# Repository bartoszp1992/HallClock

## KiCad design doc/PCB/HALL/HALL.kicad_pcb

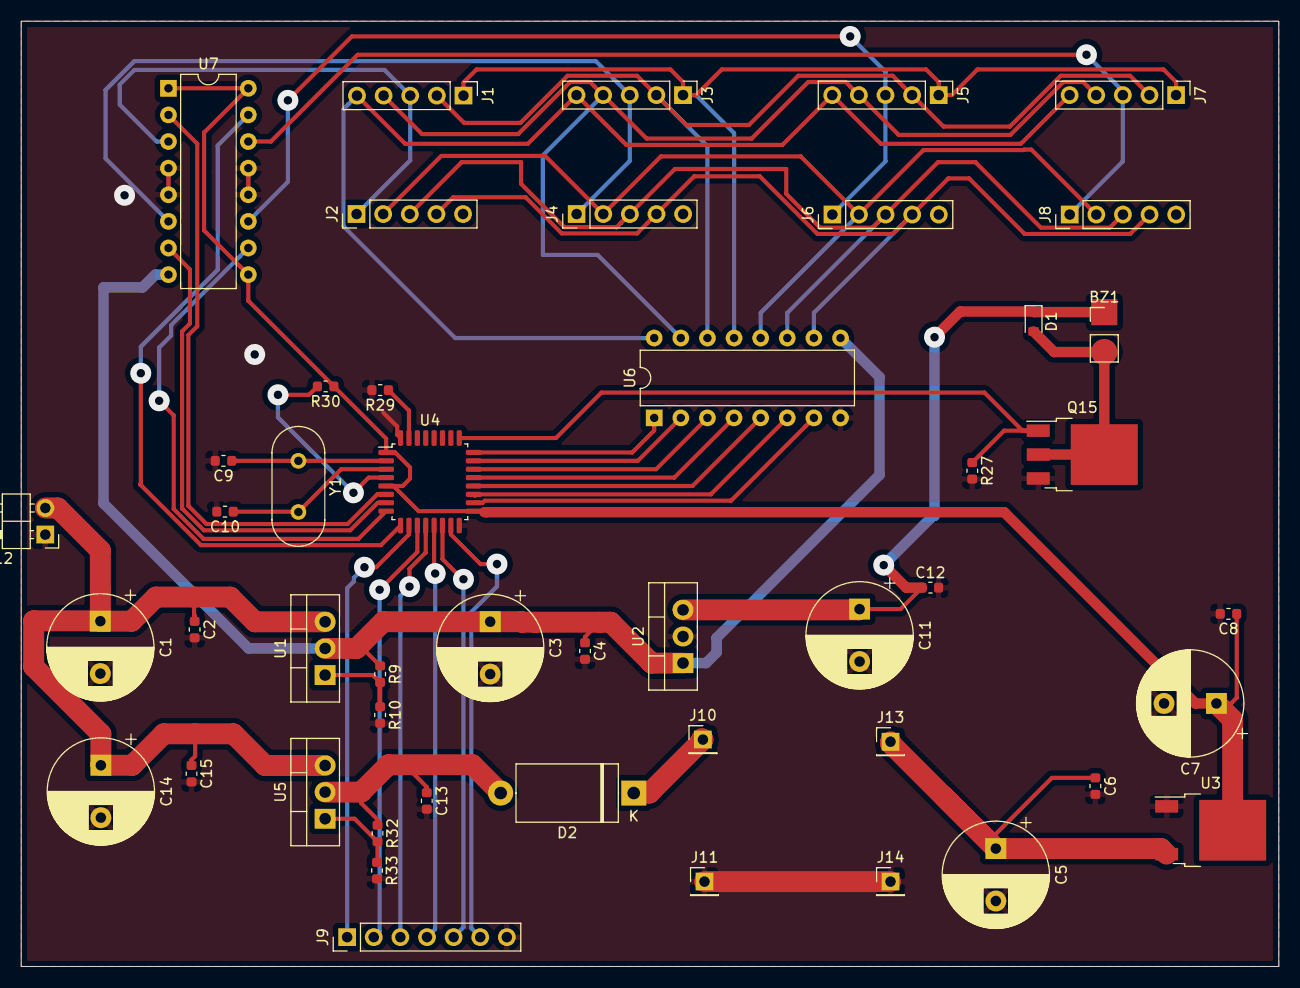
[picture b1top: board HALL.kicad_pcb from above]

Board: 2 copper layers, 120.0 x 90.2 mm, 48 parts (0 on the bottom side), 44 nets.

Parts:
BZ1: BELL; PinHeader_1x02_P2.54mm_Vertical
C1, C3, C5, C7, C11, C14: 10u; CP_Radial_D10.0mm_P5.00mm
C2, C4, C6, C8, C12, C13, C15: 100n; C_0603_1608Metric
C9, C10: 22p; C_0603_1608Metric
D1: 1n4148; D_SOD-110
D2: SR540; D_DO-27_P12.70mm_Horizontal
J1, J3, J5, J7: Conn_01x05_Female; PinHeader_1x05_P2.54mm_Vertical
J2: Digit1; PinHeader_1x05_P2.54mm_Vertical
J4: Digit2; PinHeader_1x05_P2.54mm_Vertical
J6: Digit3; PinHeader_1x05_P2.54mm_Vertical
J8: Digit4; PinHeader_1x05_P2.54mm_Vertical
J9: PILOT; PinHeader_1x07_P2.54mm_Vertical
J10: CHIN+; PinHeader_1x01_P2.54mm_Vertical
J11: CHIN-; PinHeader_1x01_P2.54mm_Vertical
J12: Vcc; PinHeader_1x02_P2.54mm_Horizontal
J13: CHOUT+; PinHeader_1x01_P2.54mm_Vertical
J14: CHOUT-; PinHeader_1x01_P2.54mm_Vertical
Q15: IRLR3636; TO-252-3_TabPin2
R9, R32: 1k; R_0603_1608Metric
R10: 13k; R_0603_1608Metric
R27, R29, R30: 10k; R_0603_1608Metric
R33: 3.4k; R_0603_1608Metric
U1, U5: LM317_3PinPackage; TO-220-3_Vertical
U2: LM7812_TO220; TO-220-3_Vertical
U3: LM1117-3.3; TO-252-2
U4: STM32F030K6Tx; LQFP-32_7x7mm_P0.8mm
U6: ULN2003; DIP-16_W7.62mm
U7: L293D; DIP-16_W7.62mm
Y1: Crystal; Crystal_HC49-4H_Vertical

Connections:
+3V3: C7.1, C8.1, R30.1, U3.2, U4.1, U4.5, U4.17, U7.1, U7.9, U7.16
+12V: BZ1.1, C11.1, C12.1, D1.1, U2.3
+15V: C3.1, C4.1, R9.1, U1.2, U2.1, U6.9, U7.8
+24V: C1.1, C2.1, C14.1, C15.1, J12.2, U1.3, U5.3
BELL: Q15.1, R27.1, U4.25
BUTTON_BACK: J9.6, U4.15
BUTTON_DOWN: J9.5, U4.14
BUTTON_ENTER: J9.3, U4.12
BUTTON_LEFT: J9.2, U4.11
BUTTON_RIGHT: J9.4, U4.13
BUTTON_UP: J9.1, U4.10
D1: U4.6, U7.2
D2: U4.7, U7.7
D3: U4.8, U7.10
D4: U4.9, U7.15
GND: C1.2, C2.2, C3.2, C4.2, C5.2, C6.2, C7.2, C8.2, C9.2, C10.2, C11.2, C12.2, C13.2, C14.2, C15.2, J9.7, J11.1, J12.1, J14.1, Q15.3, R10.2, R27.2, R29.2, R33.2, U2.2, U3.1, U4.16, U4.32, U6.8, U7.4, U7.5, U7.12, U7.13
unnamed: C5.1, C6.1, J13.1, U3.3
unnamed: BZ1.2, D1.2, Q15.2
unnamed: C9.1, U4.2, Y1.1
unnamed: C10.1, U4.3, Y1.2
unnamed: C13.1, D2.2, R32.1, U5.2
unnamed: D2.1, J10.1
unnamed: J1.1, J3.1, J5.1, J7.1, U6.13
unnamed: J1.2, J3.2, J5.2, J7.2, U6.14
unnamed: J1.3, J2.1, U7.3
unnamed: J1.4, J3.4, J5.4, J7.4, U6.15
unnamed: J1.5, J3.5, J5.5, J7.5, U6.16
unnamed: J2.2, J4.2, J6.2, J8.2, U6.12
unnamed: J2.3, J4.3, J6.3, J8.3, U6.11
unnamed: J2.4, J4.4, J6.4, J8.4, U6.10
unnamed: J3.3, J4.1, U7.6
unnamed: J5.3, J6.1, U7.11
unnamed: J7.3, J8.1, U7.14
unnamed: R9.2, R10.1, U1.1
unnamed: R29.1, U4.31
unnamed: R30.2, U4.4
unnamed: R32.2, R33.1, U5.1
SA: U4.22, U6.3
SB: U4.21, U6.4
SC: U4.18, U6.7
SD: U4.19, U6.6
SE: U4.20, U6.5
SF: U4.23, U6.2
SG: U4.24, U6.1

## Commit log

2019-09-12 initial
2019-09-12 added buttons to schematic
2019-09-13 making pbc
2019-09-16 PCB almost done
2019-09-19 new pcb
2019-11-07 proto
2020-01-20 dunno
